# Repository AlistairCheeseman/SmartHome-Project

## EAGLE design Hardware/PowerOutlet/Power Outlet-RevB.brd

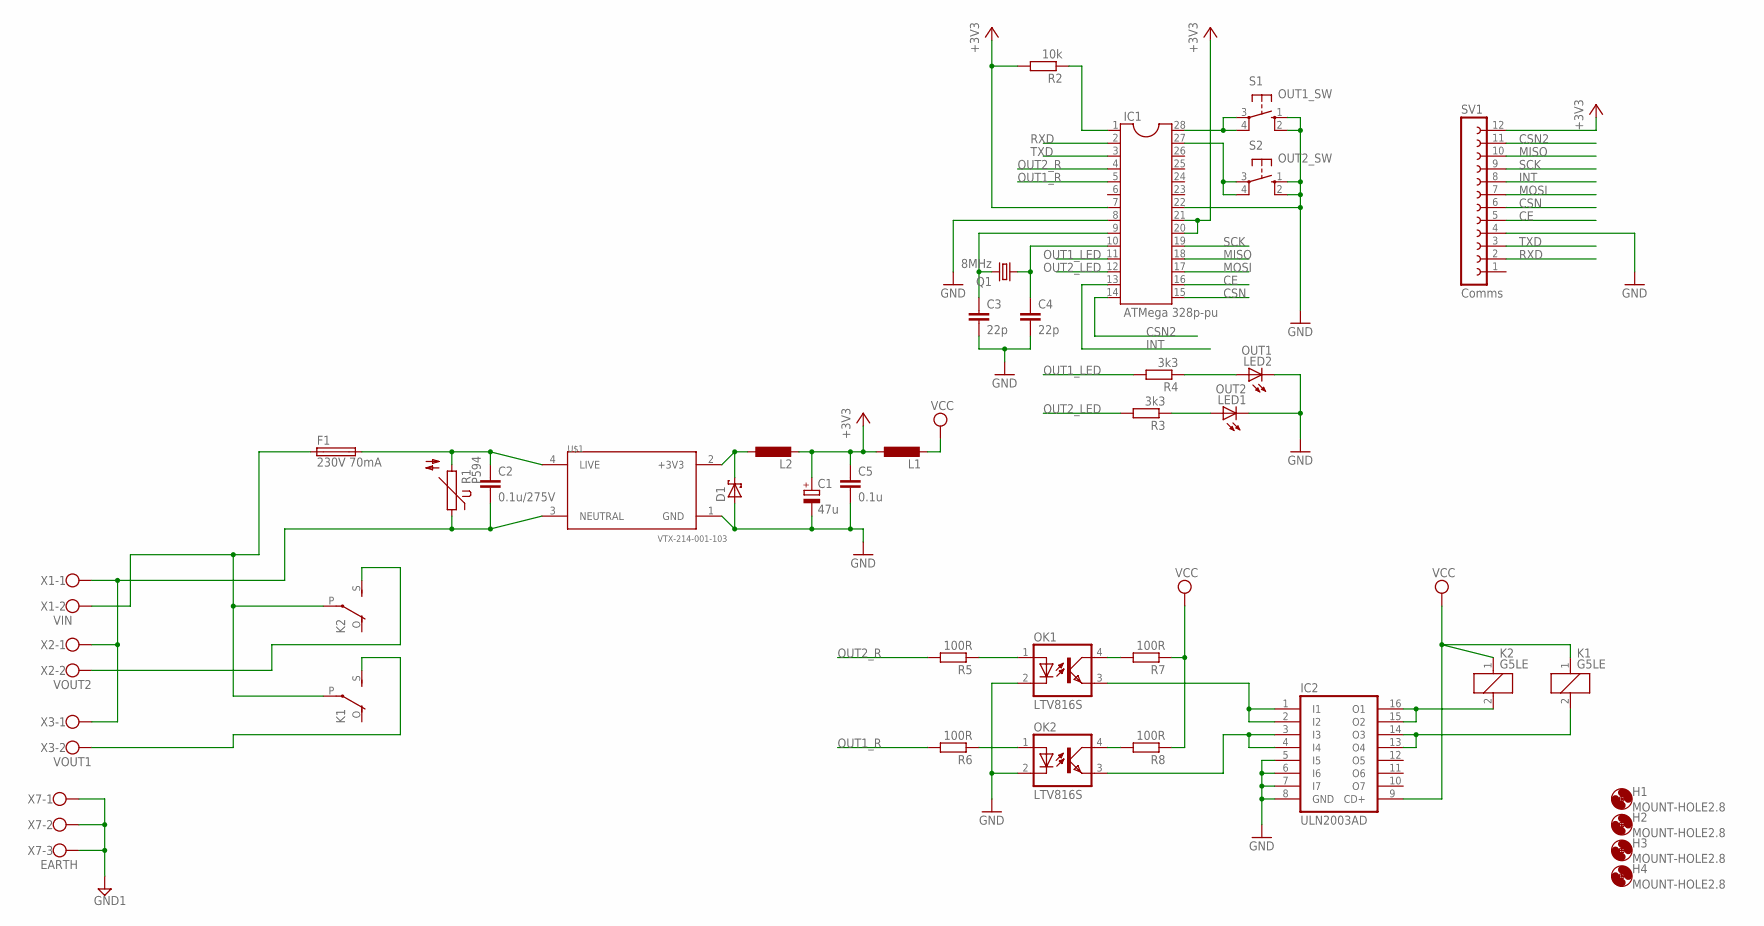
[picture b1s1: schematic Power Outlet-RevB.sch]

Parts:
C1: 47u; E2,5-6E
C2: 0.1u/275V; C150-054X183
C3, C4: 22p; C1206K
C5: 0.1u; C1206K
D1: SCHOTTKY-DIODESMC; SMC
F1: 230V 70mA; SH22,5A
H1, H2, H3, H4: MOUNT-HOLE2.8; 2,8
IC1: ATMega 328p-pu; DIL28-3
IC2: ULN2003AD; SO16
K1, K2: G5LE
L1, L2: L-EUL3225P; L3225P
LED1: OUT2; LED5MM
LED2: OUT1; LED5MM
OK1, OK2: LTV816S; DIL4-SMD
Q1: 8MHz; HC49/S
R1: P594
R2: 10k; R1206W
R3, R4: 3k3; R1206W
R5, R6, R7, R8: 100R; R1206W
S1: OUT1_SW; B3F-40XX
S2: OUT2_SW; B3F-40XX
SV1: Comms; FE12W
U$1: VTX-214-001-103; VTX214001103
X1: VIN; W237-102
X2: VOUT2; W237-102
X3: VOUT1; W237-102
X7: EARTH; W237-103

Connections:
+3V3: C1.+, C5.1, D1.C, IC1.7, IC1.20, IC1.21, L1.1, L2.1, L2.2, R2.2, SV1.12, U$1.2 (+3V3)
CE: IC1.16, SV1.5
CSN: IC1.15, SV1.6
CSN2: IC1.14, SV1.11
GND: C1.-, C3.2, C4.2, C5.2, D1.A, IC1.8, IC1.22, IC2.5 (I5), IC2.6 (I6), IC2.7 (I7), IC2.8 (GND), LED1.K (C), LED2.K (C), OK1.2 (C), OK2.2 (C), S1.1 (S), S1.2 (S1), S2.1 (S), S2.2 (S1), SV1.4, U$1.1 (GND)
GND1: X7.1, X7.2, X7.3
INT: IC1.13, SV1.8
MISO: IC1.18, SV1.10
MOSI: IC1.17, SV1.7
unnamed: F1.1, K1.P, K2.P, X1.2
unnamed: C2.1, F1.2, R1.2, U$1.4 (LIVE)
unnamed: C2.2, R1.1, U$1.3 (NEUTRAL), X1.1, X2.1, X3.1
unnamed: IC1.1, R2.1
unnamed: C3.1, IC1.9, Q1.2
unnamed: C4.1, IC1.10, Q1.1
unnamed: LED1.A, R3.1
unnamed: LED2.A, R4.1
unnamed: IC1.28, S1.3, S1.4 (P1)
unnamed: IC1.27, S2.3, S2.4 (P1)
unnamed: K2.S, X2.2
unnamed: IC2.15 (O2), IC2.16 (O1), K2.2
unnamed: IC2.13 (O4), IC2.14 (O3), K1.2
unnamed: K1.S, X3.2
unnamed: OK1.1 (A), R5.1
unnamed: OK2.1 (A), R6.1
unnamed: IC2.1 (I1), IC2.2 (I2), OK1.3 (EMIT)
unnamed: IC2.3 (I3), IC2.4 (I4), OK2.3 (EMIT)
unnamed: OK1.4 (COL), R7.2
unnamed: OK2.4 (COL), R8.2
OUT1_LED: IC1.11, R4.2
OUT1_R: IC1.5, R6.2
OUT2_LED: IC1.12, R3.2
OUT2_R: IC1.4, R5.2
RXD: IC1.2, SV1.2
SCK: IC1.19, SV1.9
TXD: IC1.3, SV1.3
VCC: IC2.9 (CD+), K1.1, K2.1, L1.2, R7.1, R8.1

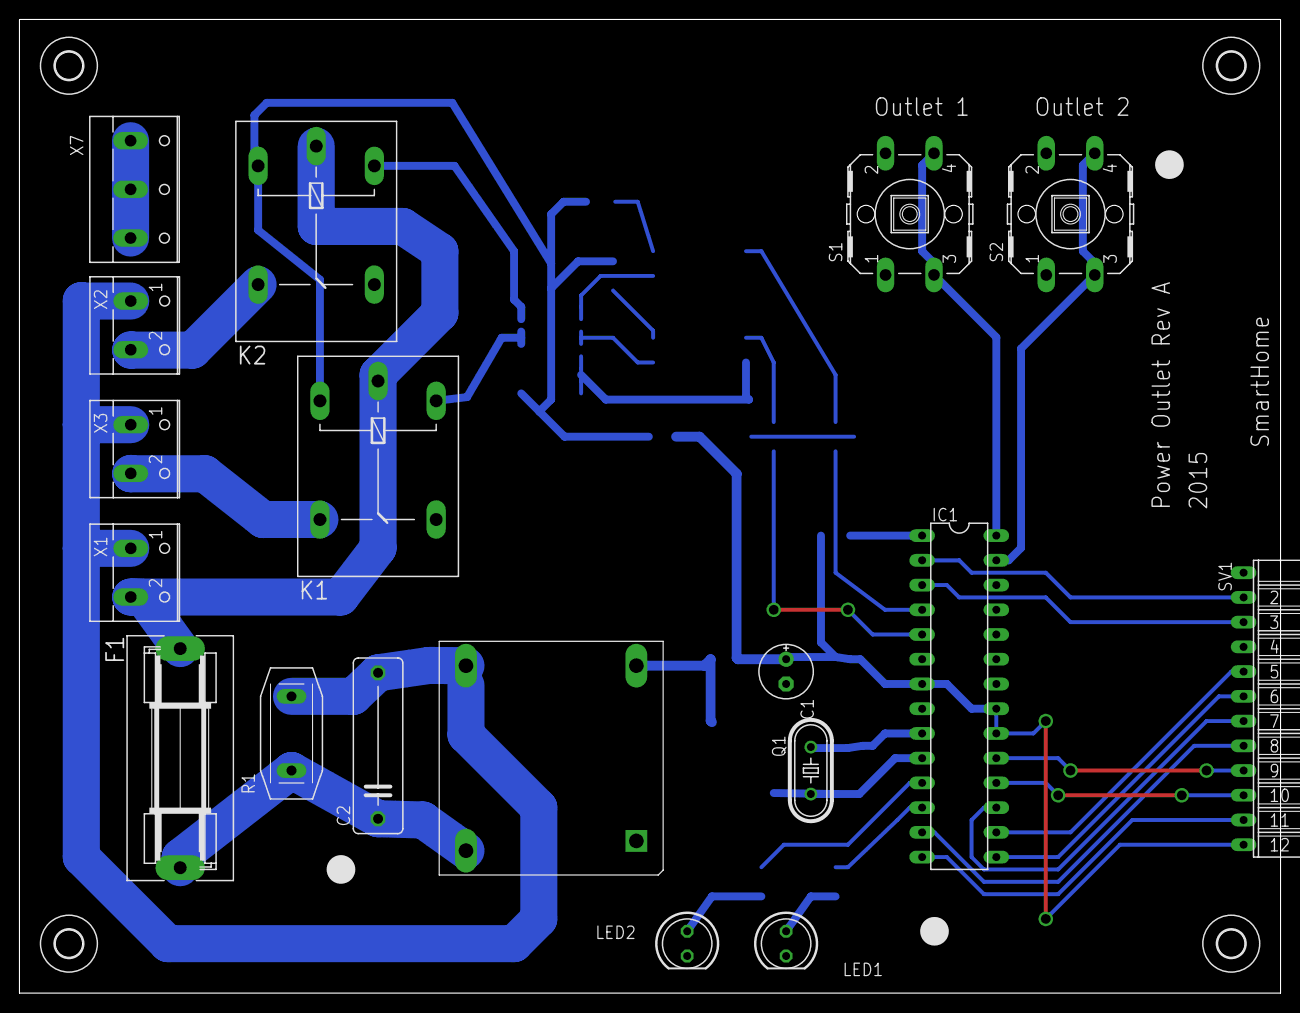
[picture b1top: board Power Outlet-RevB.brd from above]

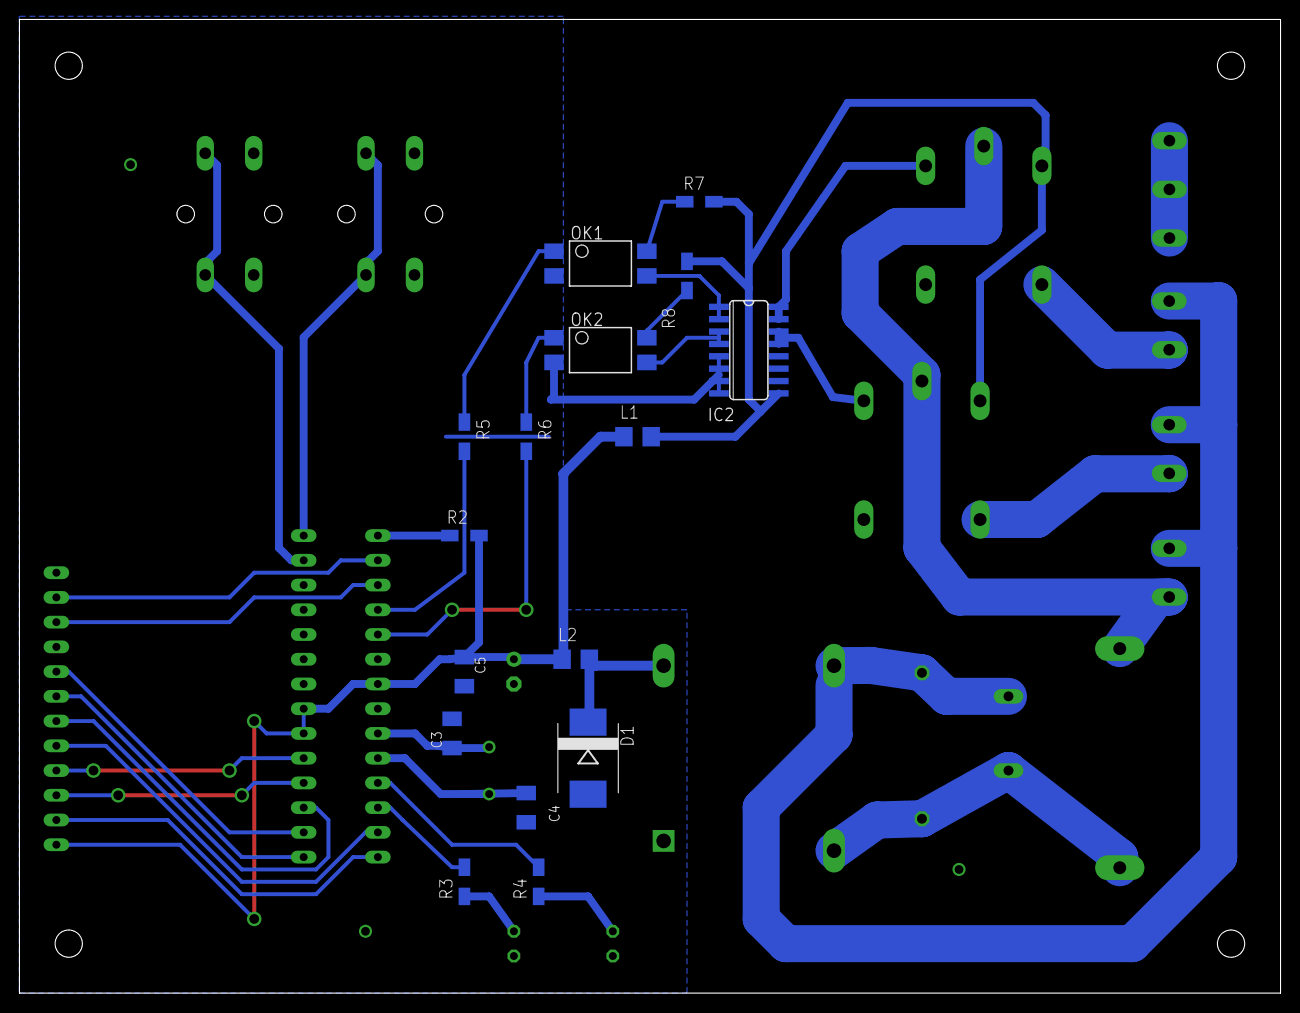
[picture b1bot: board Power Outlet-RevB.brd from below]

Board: 2 copper layers, 129.5 x 100.0 mm, 38 parts (16 on the bottom side), 37 nets.
